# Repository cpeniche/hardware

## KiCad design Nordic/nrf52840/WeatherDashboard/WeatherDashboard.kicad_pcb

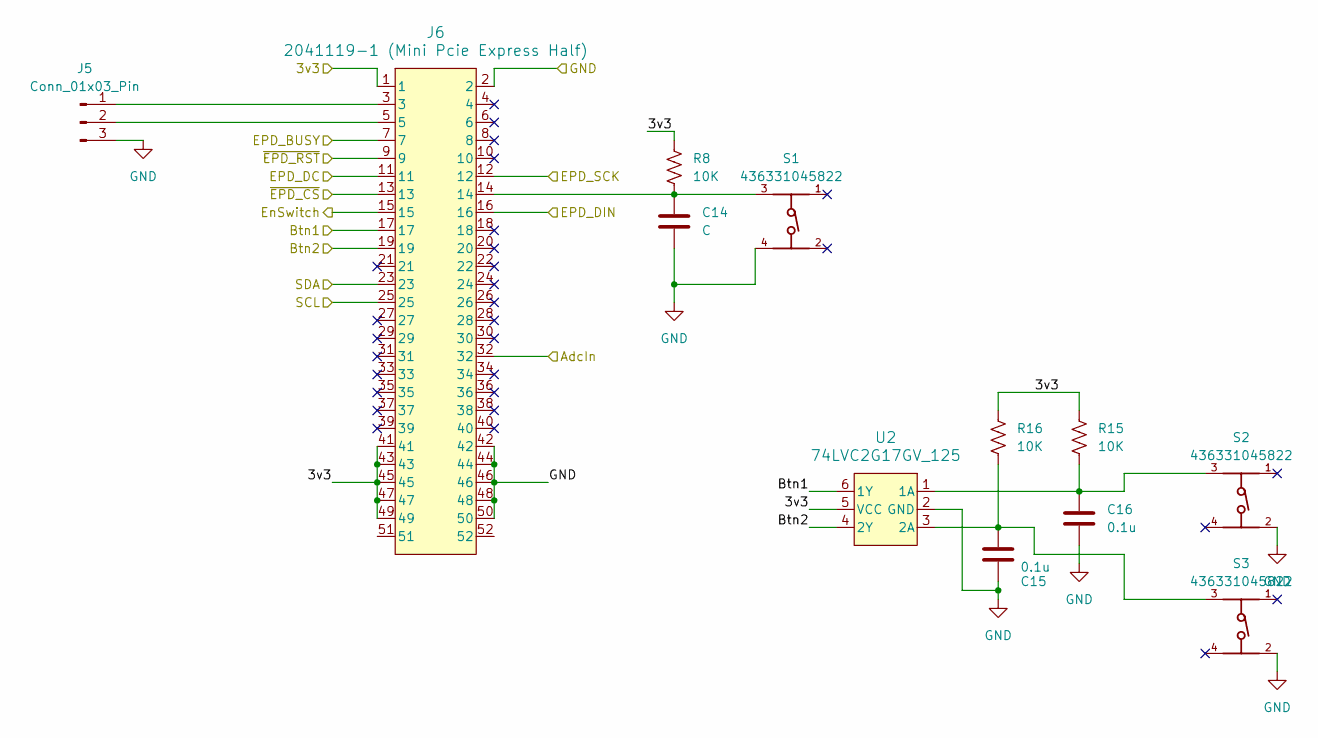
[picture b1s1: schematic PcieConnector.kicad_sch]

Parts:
C14: C; C_0805_2012Metric_Pad1.18x1.45mm_HandSolder
C15, C16: 0.1u; C_0402_1005Metric_Pad0.74x0.62mm_HandSolder
J5: Conn_01x03_Pin; PinSocket_1x03_P2.54mm_Vertical
J6: 2041119-1 (Mini Pcie Express Half); CONN_2041119-1_TEC
R8, R15, R16: 10K; R_0402_1005Metric_Pad0.72x0.64mm_HandSolder
S1, S2, S3: 436331045822; 4363X10458XX
U2: 74LVC2G17GV_125; SC-74_TSOP6_NEX

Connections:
/Display/3v3: J6.1, J6.41, J6.43, J6.45, J6.47, J6.49, R8.1, R15.1, R16.1, U2.5 (VCC); also elsewhere on the board
/Display/EPD_BUSY: J6.7; also elsewhere on the board
/Display/EPD_DC: J6.11; also elsewhere on the board
/Display/EPD_DIN: J6.16; also elsewhere on the board
/Display/EPD_SCK: J6.12; also elsewhere on the board
/Display/TSCL: J6.25; also elsewhere on the board
/Display/TSDA: J6.23; also elsewhere on the board
/Display/~EPD_CS: J6.13; also elsewhere on the board
/Display/~EPD_RST: J6.9; also elsewhere on the board
/Pcie Connector/AdcIn: J6.32; also elsewhere on the board
/Pcie Connector/Btn1: J6.17, U2.6 (1Y)
/Pcie Connector/Btn2: J6.19, U2.4 (2Y)
/Pcie Connector/EnSwitch: J6.15; also elsewhere on the board
GND: C14.2, C15.2, C16.2, J5.3, J6.2, J6.42, J6.44, J6.46, J6.48, J6.50, S1.4, S2.2, S3.2, U2.2 (GND); also elsewhere on the board
unnamed: C14.1, J6.14, R8.2, S1.3
unnamed: J5.1, J6.3
unnamed: J5.2, J6.5
unnamed: C16.1, R15.2, S2.3, U2.1 (1A)
unnamed: C15.1, R16.2, S3.3, U2.3 (2A)

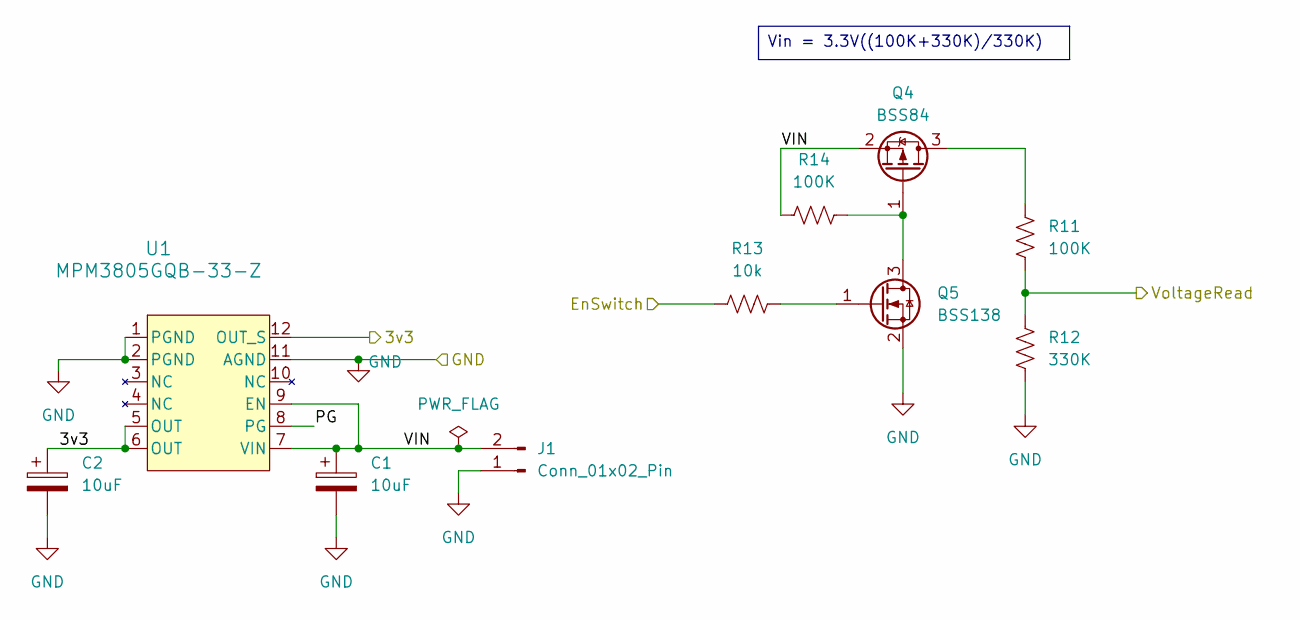
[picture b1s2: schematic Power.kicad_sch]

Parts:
C1, C2: 10uF; CP_EIA-3216-12_Kemet-S_HandSolder
J1: Conn_01x02_Pin; PinHeader_1x02_P2.54mm_Vertical
Q4: BSS84; SOT-23
Q5: BSS138; SOT-23
R11, R14: 100K; R_0402_1005Metric_Pad0.72x0.64mm_HandSolder
R12: 330K; R_0402_1005Metric_Pad0.72x0.64mm_HandSolder
R13: 10k; R_0402_1005Metric_Pad0.72x0.64mm_HandSolder
U1: MPM3805GQB-33-Z; QFN2p5x3p0x0p9_MNP

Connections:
/Display/3v3: C2.1, U1.5 (OUT), U1.6 (OUT), U1.12 (OUT_S); also elsewhere on the board
/Pcie Connector/AdcIn: R11.2, R12.1; also elsewhere on the board
/Pcie Connector/EnSwitch: R13.1; also elsewhere on the board
/Power/PG: U1.8 (PG)
/Power/VIN: C1.1, J1.2, Q4.2 (S), R14.1, U1.7 (VIN), U1.9 (EN)
GND: C1.2, C2.2, J1.1, Q5.2 (S), R12.2, U1.1 (PGND), U1.2 (PGND), U1.11 (AGND); also elsewhere on the board
unnamed: Q4.3 (D), R11.1
unnamed: Q4.1 (G), Q5.3 (D), R14.2
unnamed: Q5.1 (G), R13.2

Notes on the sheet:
Vin = 3.3V((100K+330K)/330K)

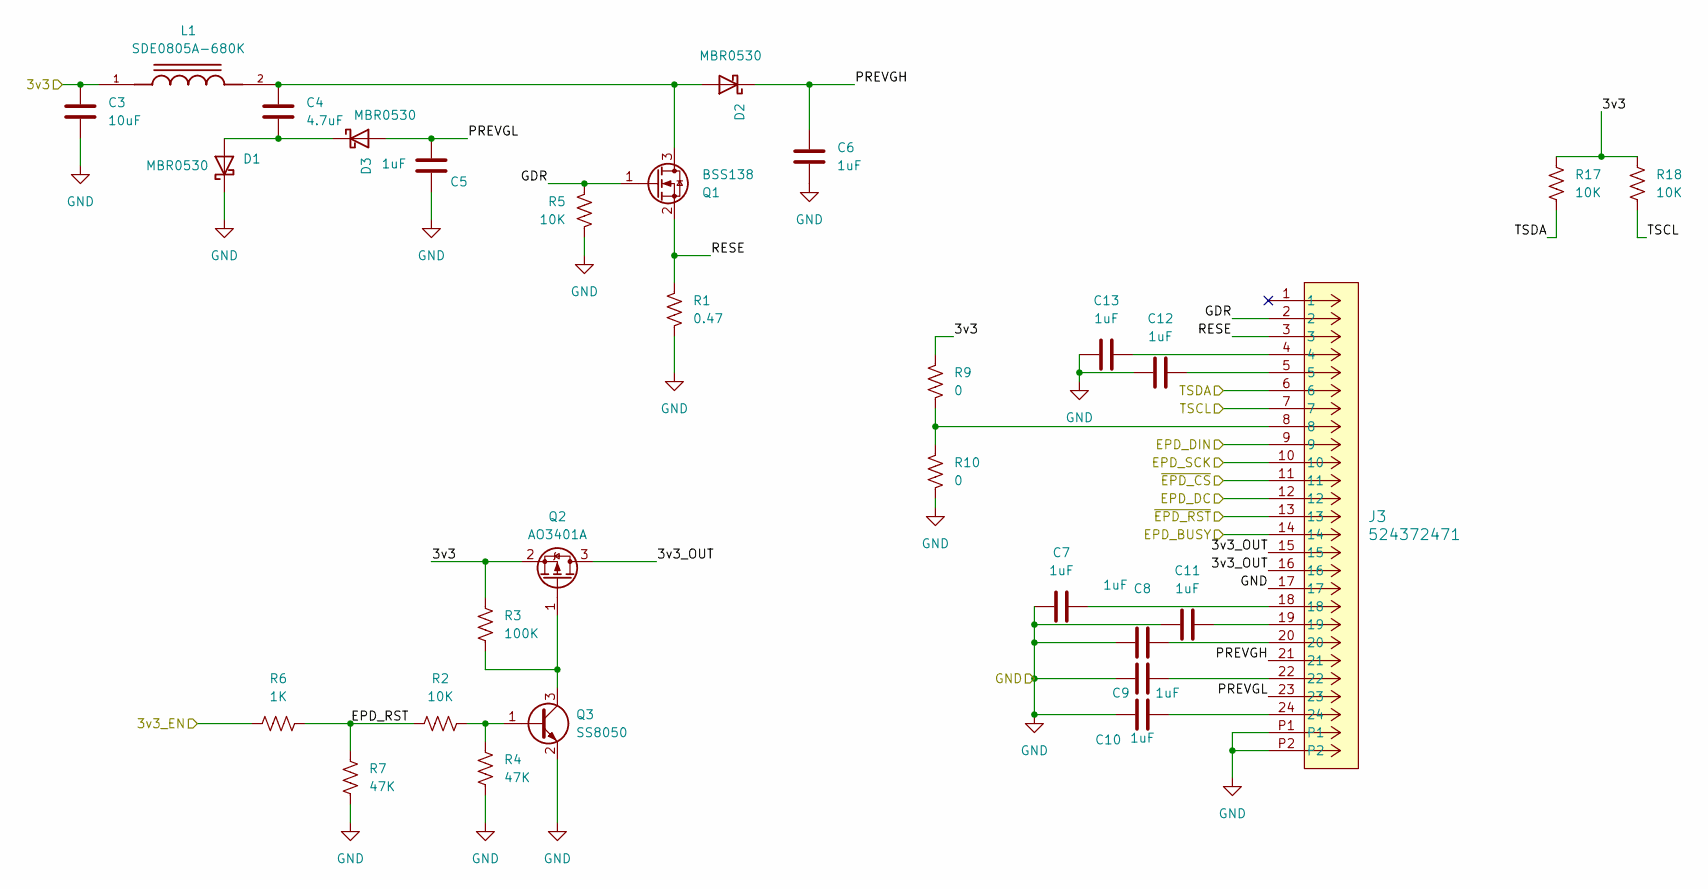
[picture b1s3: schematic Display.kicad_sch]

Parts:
C3: 10uF; C_0402_1005Metric_Pad0.74x0.62mm_HandSolder
C4: 4.7uF; C_0402_1005Metric_Pad0.74x0.62mm_HandSolder
C5, C6, C7, C8, C9, C10, C11, C12, C13: 1uF; C_0402_1005Metric_Pad0.74x0.62mm_HandSolder
D1, D2, D3: MBR0530; D_SOD-123
J3: 524372471; CON_524372471_MOL
L1: SDE0805A-680K; IND_SDE0805A-680K; PARTREV 11/19
Q1: BSS138; SOT-23_Handsoldering
Q2: AO3401A; SOT-23
Q3: SS8050; SOT-23_Handsoldering
R1: 0.47; R_0402_1005Metric_Pad0.72x0.64mm_HandSolder
R2, R5, R17, R18: 10K; R_0402_1005Metric_Pad0.72x0.64mm_HandSolder
R3: 100K; R_0402_1005Metric_Pad0.72x0.64mm_HandSolder
R4, R7: 47K; R_0402_1005Metric_Pad0.72x0.64mm_HandSolder
R6: 1K; R_0402_1005Metric_Pad0.72x0.64mm_HandSolder
R9, R10: 0; R_0402_1005Metric_Pad0.72x0.64mm_HandSolder

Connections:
/Display/3v3: C3.1, L1.1, Q2.2 (S), R3.1, R6.2, R9.1, R17.2, R18.2; also elsewhere on the board
/Display/3v3_OUT: J3.15, J3.16, Q2.3 (D)
/Display/EPD_BUSY: J3.14; also elsewhere on the board
/Display/EPD_DC: J3.12; also elsewhere on the board
/Display/EPD_DIN: J3.9; also elsewhere on the board
/Display/EPD_RST: R2.1, R6.1, R7.2
/Display/EPD_SCK: J3.10; also elsewhere on the board
/Display/GDR: J3.2, Q1.1 (G), R5.2
/Display/PREVGH: C6.1, D2.1 (K), J3.21
/Display/PREVGL: C5.1, D3.2 (A), J3.23
/Display/RESE: J3.3, Q1.2 (S), R1.1
/Display/TSCL: J3.7, R18.1; also elsewhere on the board
/Display/TSDA: J3.6, R17.1; also elsewhere on the board
/Display/~EPD_CS: J3.11; also elsewhere on the board
/Display/~EPD_RST: J3.13; also elsewhere on the board
GND: C3.2, C5.2, C6.2, C7.1, C8.1, C9.1, C10.1, C11.1, C12.1, C13.1, D1.1 (K), J3.17, J3.P1, J3.P2, Q3.2 (E), R1.2, R4.2, R5.1, R7.1, R10.2; also elsewhere on the board
unnamed: C7.2, J3.18
unnamed: C8.2, J3.20
unnamed: C9.2, J3.22
unnamed: C10.2, J3.24
unnamed: C11.2, J3.19
unnamed: C12.2, J3.5
unnamed: C13.2, J3.4
unnamed: C4.2, D1.2 (A), D3.1 (K)
unnamed: C4.1, D2.2 (A), L1.2, Q1.3 (D)
unnamed: J3.8, R9.2, R10.1
unnamed: Q2.1 (G), Q3.3 (C), R3.2
unnamed: Q3.1 (B), R2.2, R4.1

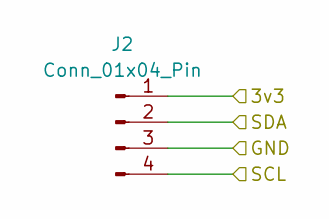
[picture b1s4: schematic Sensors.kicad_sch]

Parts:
J2: Conn_01x04_Pin; PinHeader_1x04_P2.54mm_Vertical

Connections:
/Display/3v3: J2.1; also elsewhere on the board
/Display/TSCL: J2.4; also elsewhere on the board
/Display/TSDA: J2.2; also elsewhere on the board
GND: J2.3; also elsewhere on the board

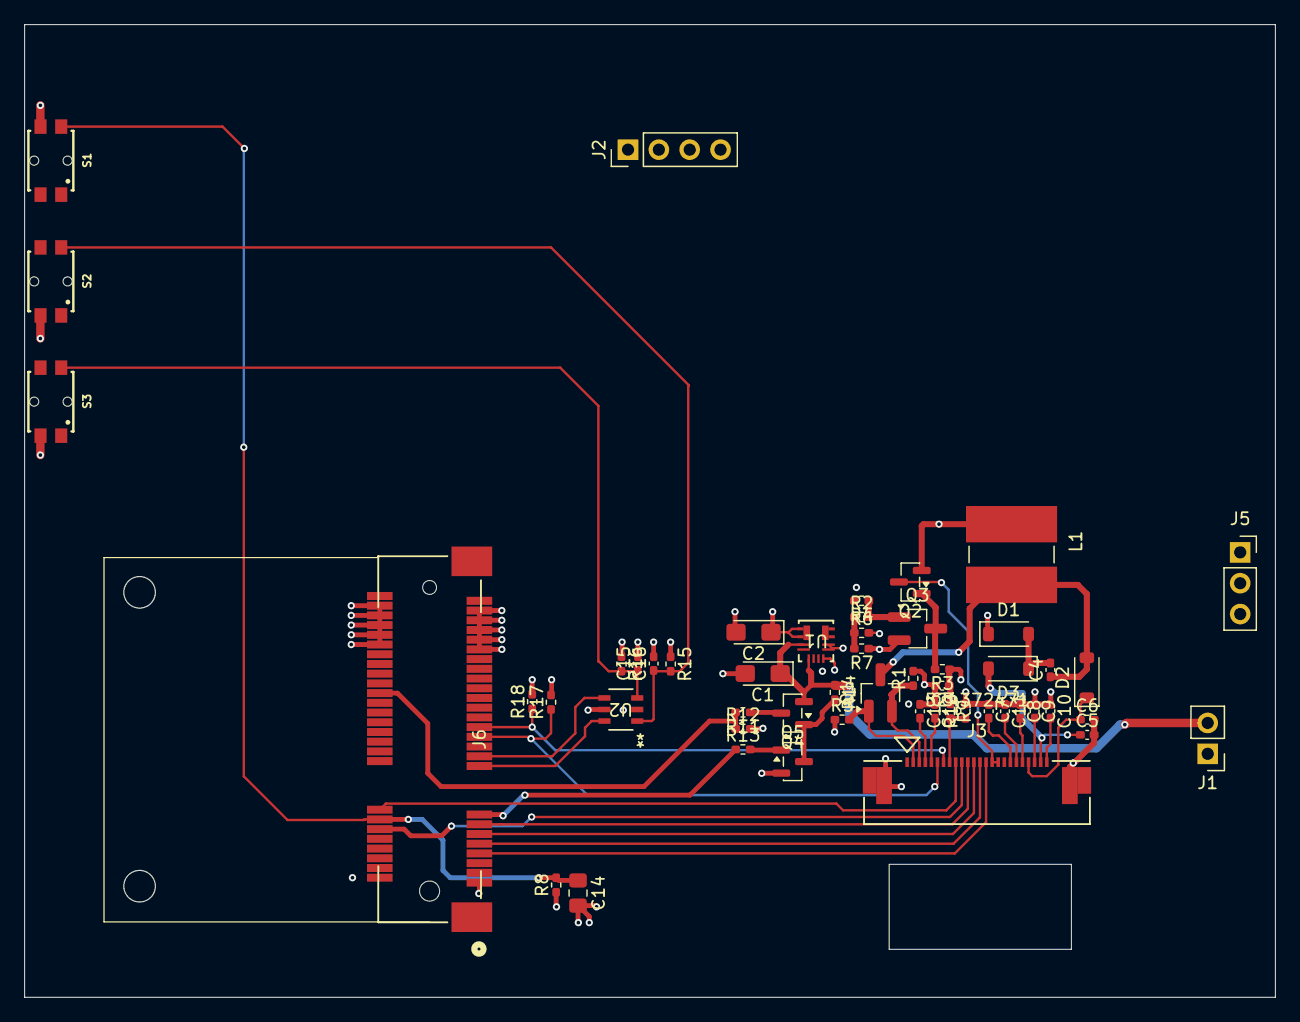
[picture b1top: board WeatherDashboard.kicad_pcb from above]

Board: 4 copper layers, 102.9 x 80.0 mm, 53 parts (0 on the bottom side), 41 nets.

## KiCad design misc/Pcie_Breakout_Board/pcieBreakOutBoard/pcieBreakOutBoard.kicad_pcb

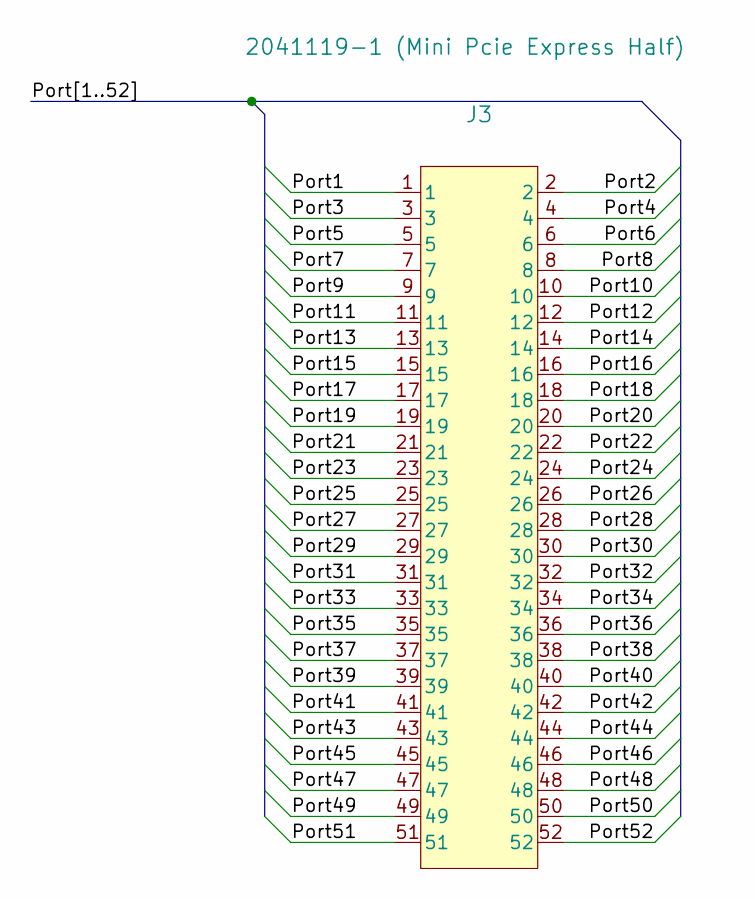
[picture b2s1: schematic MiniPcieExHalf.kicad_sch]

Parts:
J3: 2041119-1 (Mini Pcie Express Half); BUS_PCI_Express_Mini_Half

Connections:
/MiniPcieExHalf/Port1: J3.1
/MiniPcieExHalf/Port2: J3.2
/MiniPcieExHalf/Port3: J3.3
/MiniPcieExHalf/Port4: J3.4
/MiniPcieExHalf/Port5: J3.5
/MiniPcieExHalf/Port6: J3.6
/MiniPcieExHalf/Port7: J3.7
/MiniPcieExHalf/Port8: J3.8
/MiniPcieExHalf/Port9: J3.9
/MiniPcieExHalf/Port10: J3.10
/MiniPcieExHalf/Port11: J3.11
/MiniPcieExHalf/Port12: J3.12
/MiniPcieExHalf/Port13: J3.13
/MiniPcieExHalf/Port14: J3.14
/MiniPcieExHalf/Port15: J3.15
/MiniPcieExHalf/Port16: J3.16
/MiniPcieExHalf/Port17: J3.17
/MiniPcieExHalf/Port18: J3.18
/MiniPcieExHalf/Port19: J3.19
/MiniPcieExHalf/Port20: J3.20
/MiniPcieExHalf/Port21: J3.21
/MiniPcieExHalf/Port22: J3.22
/MiniPcieExHalf/Port23: J3.23
/MiniPcieExHalf/Port24: J3.24
/MiniPcieExHalf/Port25: J3.25
/MiniPcieExHalf/Port26: J3.26
/MiniPcieExHalf/Port27: J3.27
/MiniPcieExHalf/Port28: J3.28
/MiniPcieExHalf/Port29: J3.29
/MiniPcieExHalf/Port30: J3.30
/MiniPcieExHalf/Port31: J3.31
/MiniPcieExHalf/Port32: J3.32
/MiniPcieExHalf/Port33: J3.33
/MiniPcieExHalf/Port34: J3.34
/MiniPcieExHalf/Port35: J3.35
/MiniPcieExHalf/Port36: J3.36
/MiniPcieExHalf/Port37: J3.37
/MiniPcieExHalf/Port38: J3.38
/MiniPcieExHalf/Port39: J3.39
/MiniPcieExHalf/Port40: J3.40
/MiniPcieExHalf/Port41: J3.41
/MiniPcieExHalf/Port42: J3.42
/MiniPcieExHalf/Port43: J3.43
/MiniPcieExHalf/Port44: J3.44
/MiniPcieExHalf/Port45: J3.45
/MiniPcieExHalf/Port46: J3.46
/MiniPcieExHalf/Port47: J3.47
/MiniPcieExHalf/Port48: J3.48
/MiniPcieExHalf/Port49: J3.49
/MiniPcieExHalf/Port50: J3.50
/MiniPcieExHalf/Port51: J3.51
/MiniPcieExHalf/Port52: J3.52

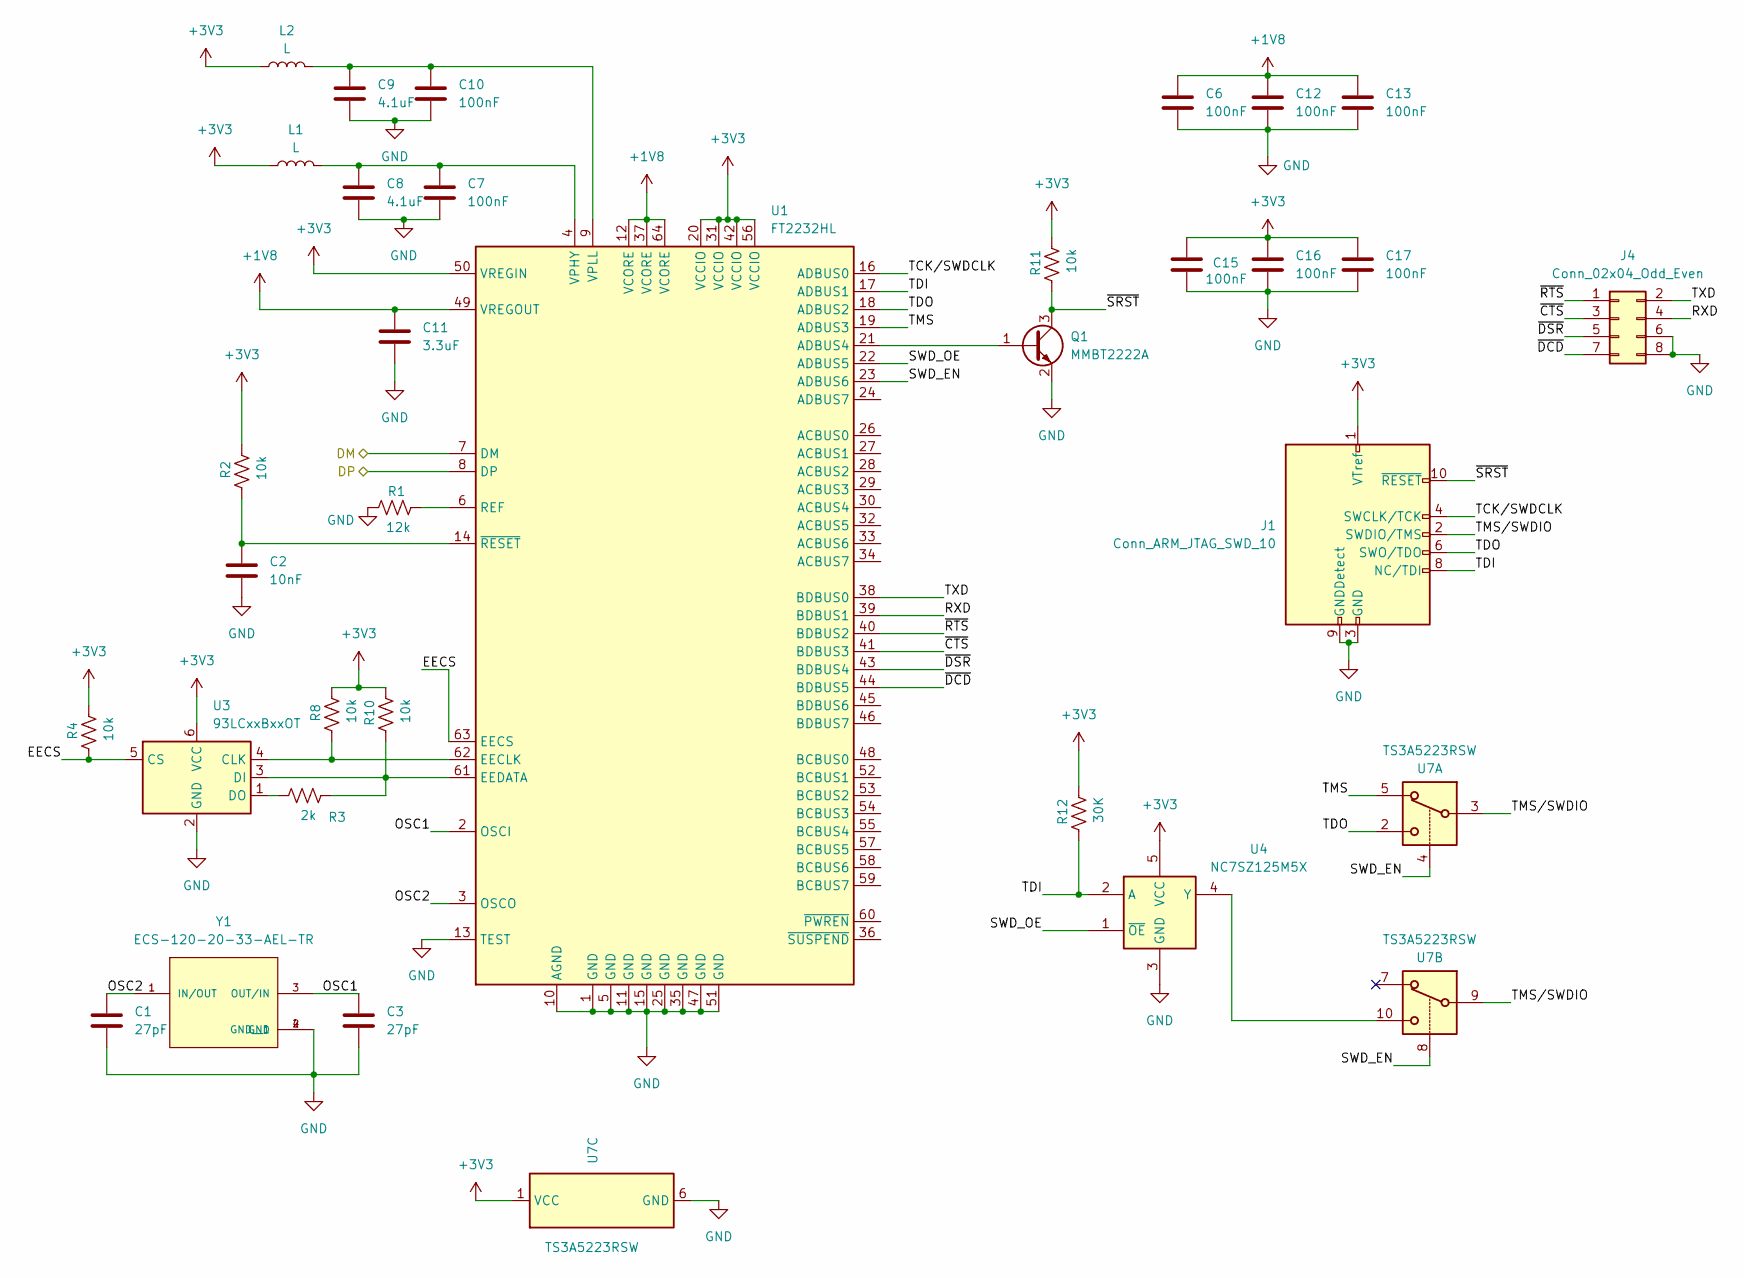
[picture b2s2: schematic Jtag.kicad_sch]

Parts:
C1, C3: 27pF; C_0402_1005Metric_Pad0.74x0.62mm_HandSolder
C2: 10nF; C_0402_1005Metric_Pad0.74x0.62mm_HandSolder
C6, C7, C10, C12, C13, C15, C16, C17: 100nF; C_0402_1005Metric_Pad0.74x0.62mm_HandSolder
C8, C9: 4.1uF; C_0402_1005Metric_Pad0.74x0.62mm_HandSolder
C11: 3.3uF; C_0402_1005Metric_Pad0.74x0.62mm_HandSolder
J1: Conn_ARM_JTAG_SWD_10; PinHeader_2x05_P1.27mm_Vertical
J4: Conn_02x04_Odd_Even; PinHeader_2x04_P2.54mm_Vertical
L1, L2: L; L_0402_1005Metric_Pad0.77x0.64mm_HandSolder
Q1: MMBT2222A; SOT-23_Handsoldering
R1: 12k; R_0402_1005Metric_Pad0.72x0.64mm_HandSolder
R2, R4, R8, R10, R11: 10k; R_0402_1005Metric_Pad0.72x0.64mm_HandSolder
R3: 2k; R_0402_1005Metric_Pad0.72x0.64mm_HandSolder
R12: 30K; R_0402_1005Metric_Pad0.72x0.64mm_HandSolder
U1: FT2232HL; LQFP-64_10x10mm_P0.5mm
U3: 93LCxxBxxOT; SOT-23-6
U4: NC7SZ125M5X; SOT-23-5
U7: TS3A5223RSW; Texas_RSW0010A_UQFN-10_1.4x1.8mm_P0.4mm
Y1: ECS-120-20-33-AEL-TR; XTAL_ECS-120-20-33-AEL-TR

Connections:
+1V8: C6.1, C11.1, C12.1, C13.1, U1.12 (VCORE), U1.37 (VCORE), U1.49 (VREGOUT), U1.64 (VCORE)
+3V3: C15.1, C16.1, C17.1, J1.1 (VTref), L1.1, L2.1, R2.2, R4.2, R8.2, R10.2, R11.2, R12.2, U1.20 (VCCIO), U1.31 (VCCIO), U1.42 (VCCIO), U1.50 (VREGIN), U1.56 (VCCIO), U3.6 (VCC), U4.5 (VCC), U7.1 (VCC); also elsewhere on the board
/Jtag/DM: U1.7 (DM)
/Jtag/DP: U1.8 (DP)
/Jtag/EECS: R4.1, U1.63 (EECS), U3.5 (CS)
/Jtag/OSC1: C3.1, U1.2 (OSCI), Y1.3 (OUT/IN)
/Jtag/OSC2: C1.1, U1.3 (OSCO), Y1.1 (IN/OUT)
/Jtag/RXD: J4.4, U1.39 (BDBUS1)
/Jtag/SWD_EN: U1.23 (ADBUS6), U7.4, U7.8
/Jtag/SWD_OE: U1.22 (ADBUS5), U4.1 (~OE)
/Jtag/TCK/SWDCLK: J1.4 (SWCLK/TCK), U1.16 (ADBUS0)
/Jtag/TDI: J1.8 (NC/TDI), R12.1, U1.17 (ADBUS1), U4.2 (A)
/Jtag/TDO: J1.6 (SWO/TDO), U1.18 (ADBUS2), U7.2
/Jtag/TMS: U1.19 (ADBUS3), U7.5
/Jtag/TMS/SWDIO: J1.2 (SWDIO/TMS), U7.3, U7.9
/Jtag/TXD: J4.2, U1.38 (BDBUS0)
/Jtag/~CTS: J4.3, U1.41 (BDBUS3)
/Jtag/~DCD: J4.7, U1.44 (BDBUS5)
/Jtag/~DSR: J4.5, U1.43 (BDBUS4)
/Jtag/~RTS: J4.1, U1.40 (BDBUS2)
/Jtag/~SRST: J1.10 (~RESET), Q1.3 (C), R11.1
GND: C1.2, C2.2, C3.2, C6.2, C7.2, C8.2, C9.2, C10.2, C11.2, C12.2, C13.2, C15.2, C16.2, C17.2, J1.3 (GND), J1.5 (GND), J1.9 (GNDDetect), J4.6, J4.8, Q1.2 (E), R1.1, U1.1 (GND), U1.5 (GND), U1.10 (AGND), U1.11 (GND), U1.13 (TEST), U1.15 (GND), U1.25 (GND), U1.35 (GND), U1.47 (GND), U1.51 (GND), U3.2 (GND), U4.3 (GND), U7.6 (GND), Y1.2 (GND), Y1.4 (GND__1); also elsewhere on the board
unnamed: Q1.1 (B), U1.21 (ADBUS4)
unnamed: R8.1, U1.62 (EECLK), U3.4 (CLK)
unnamed: R3.2, R10.1, U1.61 (EEDATA), U3.3 (DI)
unnamed: R1.2, U1.6 (REF)
unnamed: C7.1, C8.1, L1.2, U1.4 (VPHY)
unnamed: C9.1, C10.1, L2.2, U1.9 (VPLL)
unnamed: C2.1, R2.1, U1.14 (~RESET)
unnamed: R3.1, U3.1 (DO)
unnamed: U4.4 (Y), U7.10

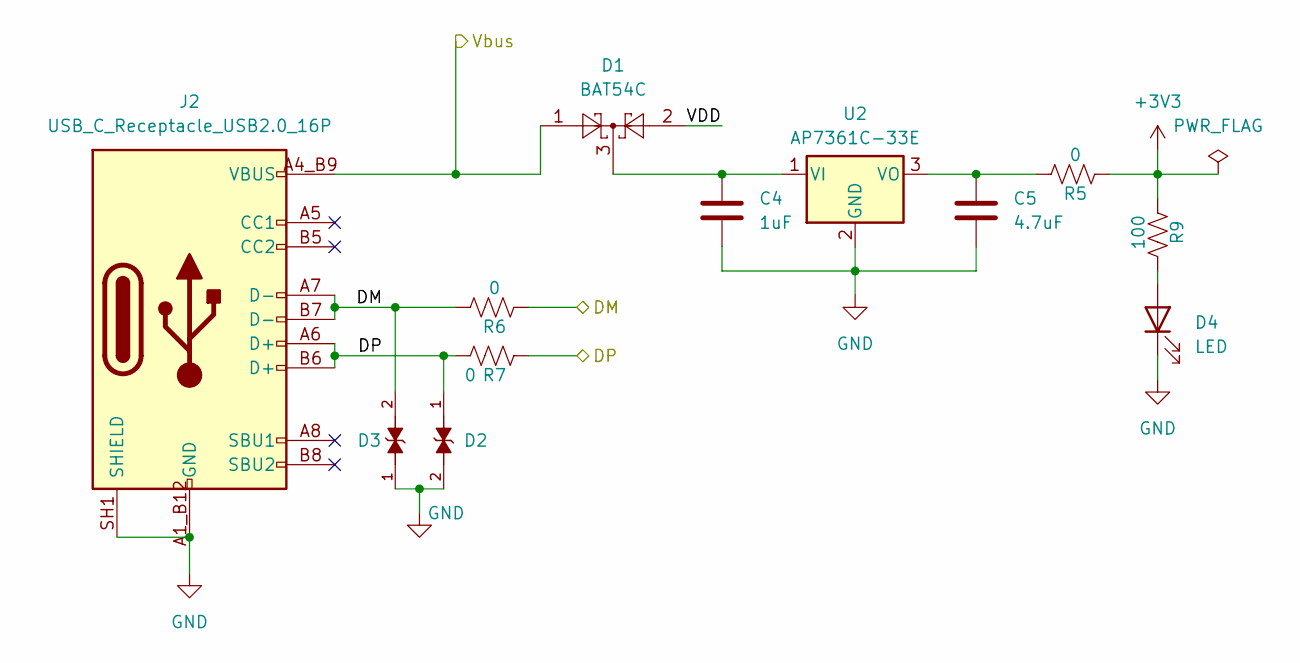
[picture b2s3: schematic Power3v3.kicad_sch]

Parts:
C4: 1uF; C_0402_1005Metric_Pad0.74x0.62mm_HandSolder
C5: 4.7uF; C_0402_1005Metric_Pad0.74x0.62mm_HandSolder
D1: BAT54C; SOT-23
D2, D3: PGB1010603NR; DIOC1608X36N
D4: LED; LED_0402_1005Metric
J2: USB_C_Receptacle_USB2.0_16P; AMPHENOL_GSB1C41110SSHR; PARTREV AX1
R5, R6, R7: 0; R_0402_1005Metric_Pad0.72x0.64mm_HandSolder
R9: 100; R_0402_1005Metric_Pad0.72x0.64mm_HandSolder
U2: AP7361C-33E; SOT-223-3_TabPin2

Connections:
+3V3: R5.2, R9.2; also elsewhere on the board
/Power/DM: D3.2, J2.A7 (D-), J2.B7 (D-), R6.1, R6.2
/Power/DP: D2.1, J2.A6 (D+), J2.B6 (D+), R7.1, R7.2
/Power/VDD: D1.2
/Power/Vbus: D1.1, J2.A4_B9 (VBUS), J2.B4_A9 (VBUS)
GND: C4.2, C5.2, D2.2, D3.1, D4.1 (K), J2.A1_B12 (GND), J2.B1_A12 (GND), J2.SH1 (SHIELD), U2.2 (GND); also elsewhere on the board
unnamed: D4.2 (A), R9.1
unnamed: C4.1, D1.3, U2.1 (VI)
unnamed: C5.1, R5.1, U2.3 (VO)

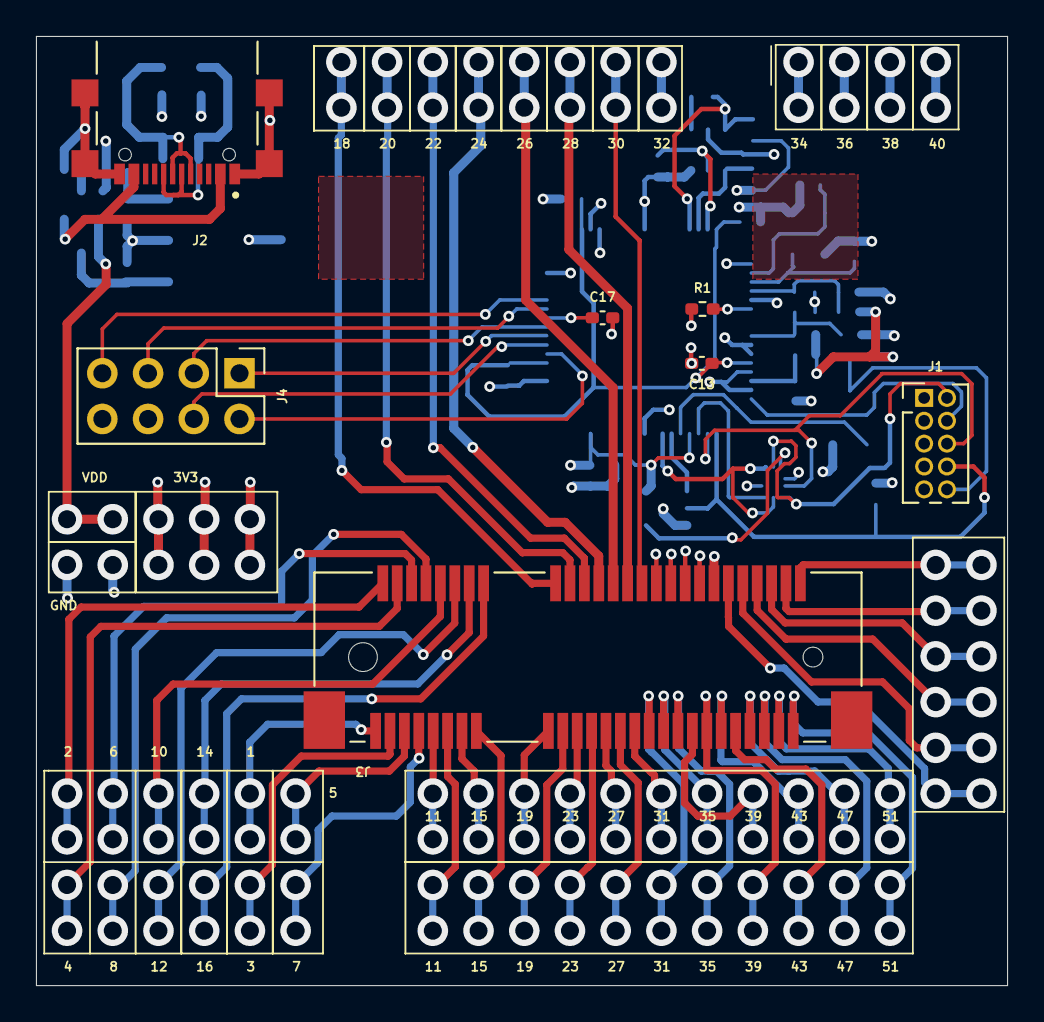
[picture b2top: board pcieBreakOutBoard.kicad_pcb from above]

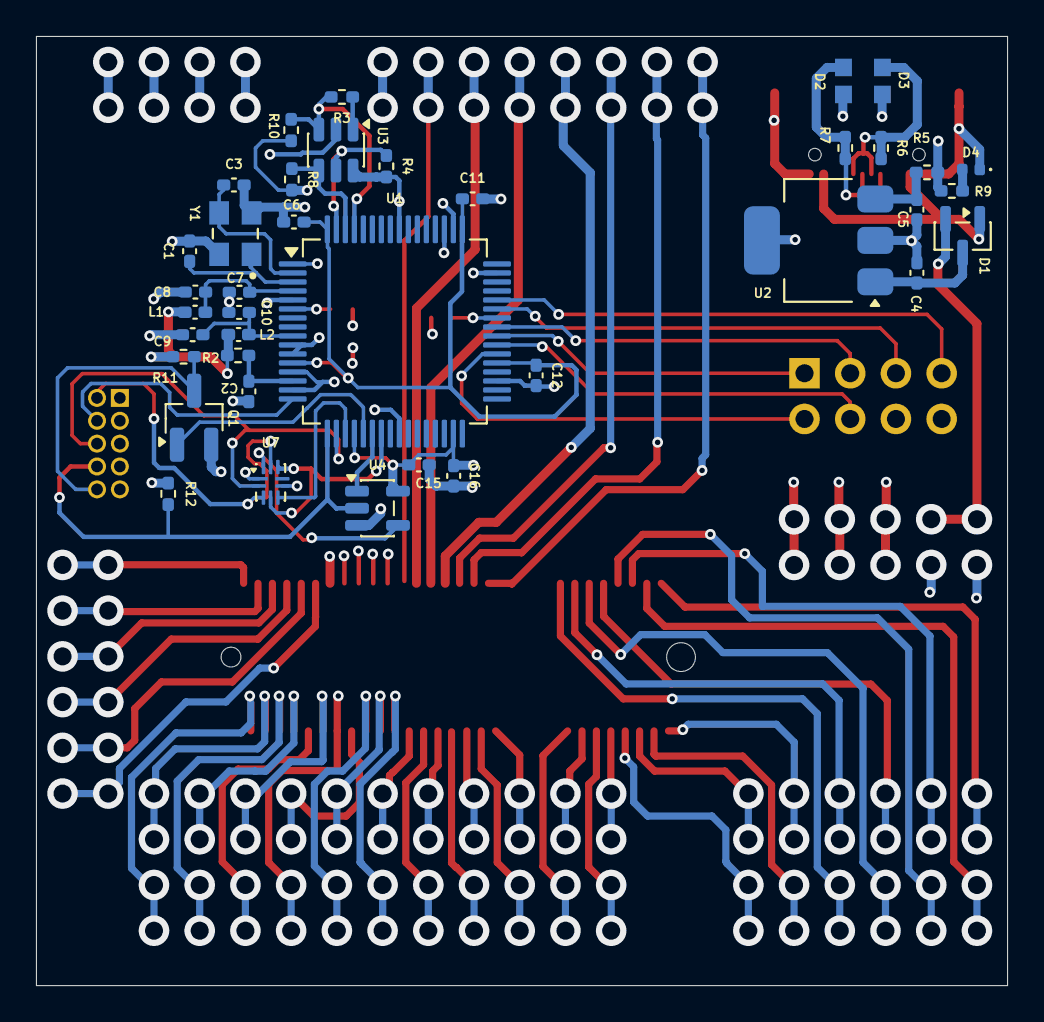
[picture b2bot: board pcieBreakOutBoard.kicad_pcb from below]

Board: 4 copper layers, 54.0 x 52.7 mm, 45 parts (38 on the bottom side), 35 nets.

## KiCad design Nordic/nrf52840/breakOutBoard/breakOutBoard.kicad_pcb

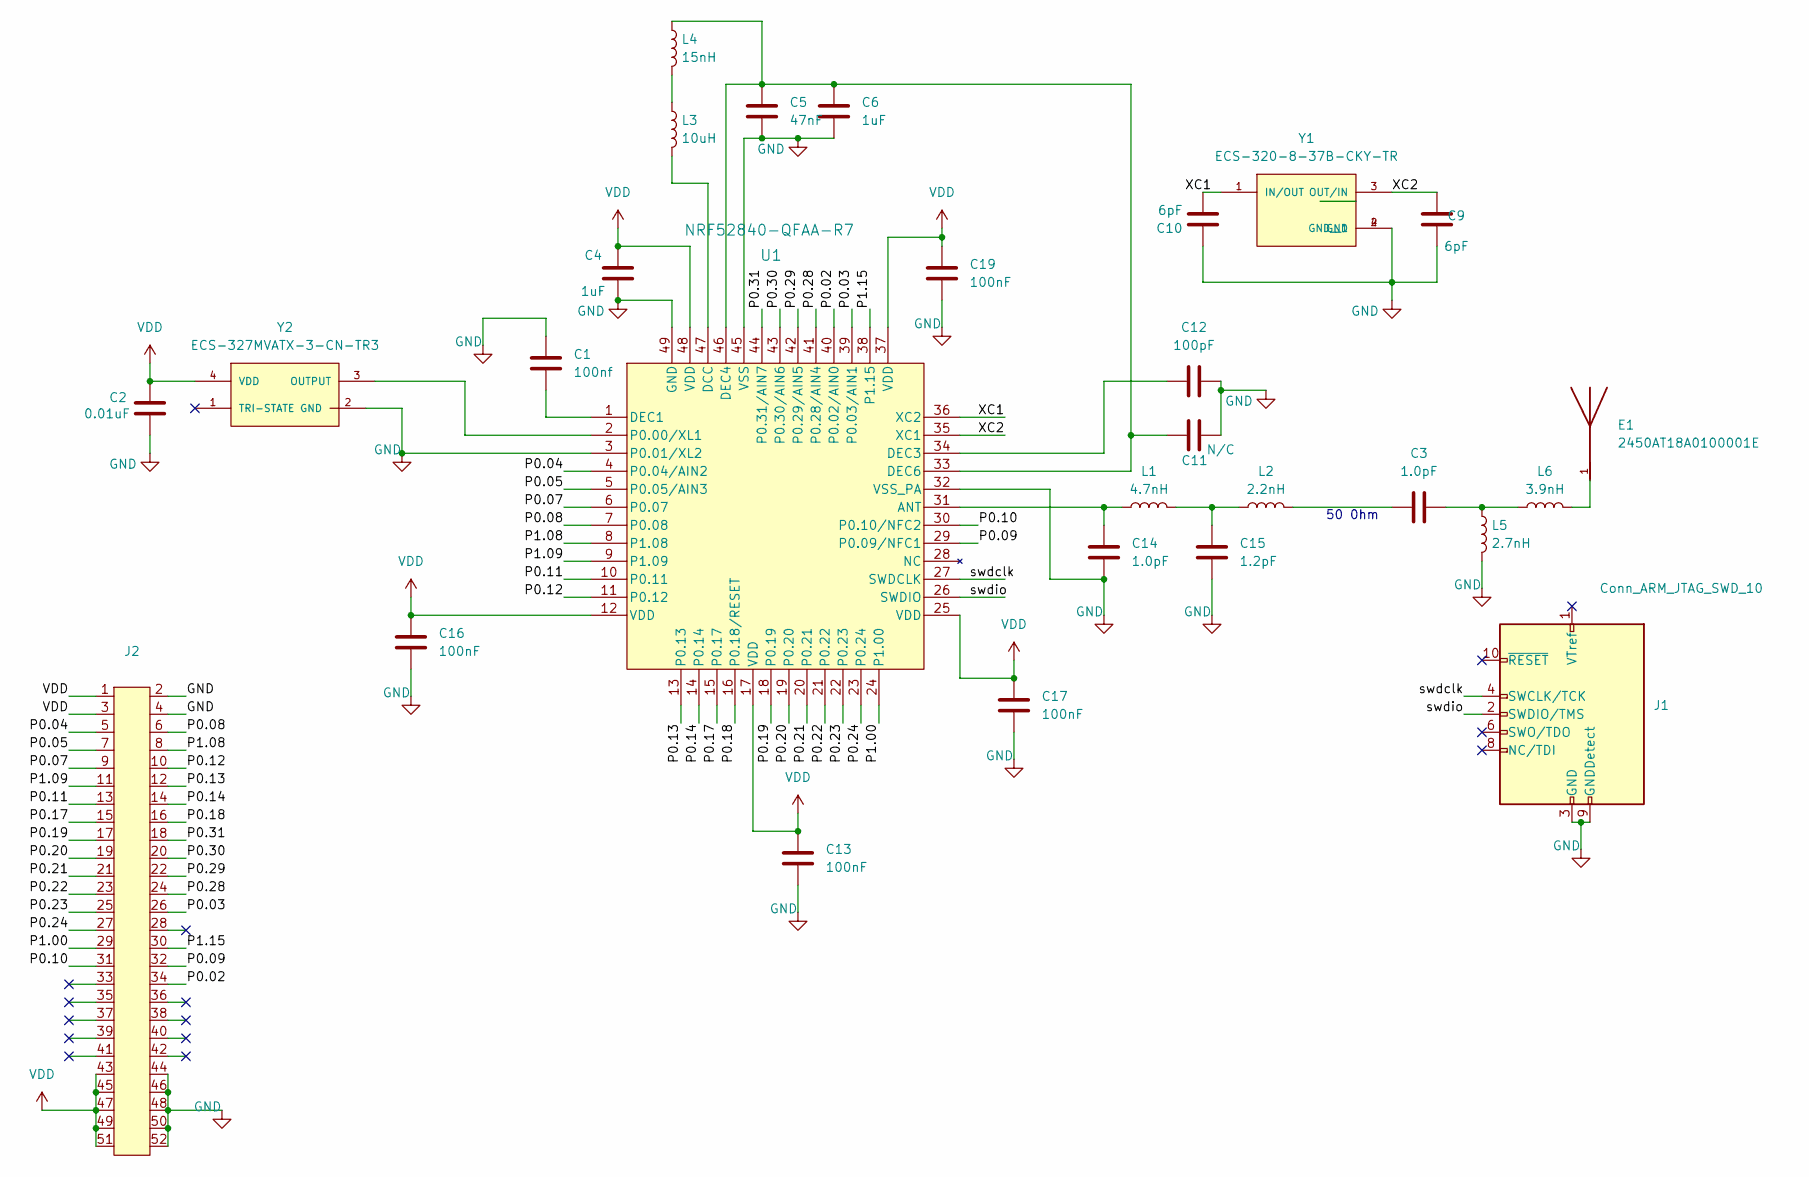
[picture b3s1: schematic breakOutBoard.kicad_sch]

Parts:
C1: 100nf; C_0201_0603Metric
C2: 0.01uF; C_0201_0603Metric
C3, C14: 1.0pF; C_0201_0603Metric
C4, C6: 1uF; C_0201_0603Metric
C5: 47nF; C_0201_0603Metric
C9, C10: 6pF; C_0201_0603Metric
C11: N/C; C_0201_0603Metric
C12: 100pF; C_0201_0603Metric
C13, C16, C17, C19: 100nF; C_0201_0603Metric
C15: 1.2pF; C_0201_0603Metric
E1: 2450AT18A0100001E; XCVR_2450AT18A0100001E; PARTREV 4.0
J1: Conn_ARM_JTAG_SWD_10; PinHeader_2x05_P1.27mm_Vertical
J2: Mini PCI express Half
L1: 4.7nH; L_0201_0603Metric
L2: 2.2nH; L_0201_0603Metric
L3: 10uH; L_0603_1608Metric
L4: 15nH; L_0201_0603Metric
L5: 2.7nH; L_0201_0603Metric
L6: 3.9nH; L_0201_0603Metric
U1: NRF52840-QFAA-R7; QFN-48-1EP_6x6mm_P0.4mm_EP4.6x4.6mm
Y1: ECS-320-8-37B-CKY-TR; XTAL_ECS-160-9-37-CKM-TR; PARTREV 2017
Y2: ECS-327MVATX-3-CN-TR3; OSC_ECS-2333-160-BN-TR; PARTREV N/A

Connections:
/P0.02: J2.34, U1.40 (P0.02/AIN0)
/P0.03: J2.26, U1.39 (P0.03/AIN1)
/P0.04: J2.5, U1.4 (P0.04/AIN2)
/P0.05: J2.7, U1.5 (P0.05/AIN3)
/P0.07: J2.9, U1.6 (P0.07)
/P0.08: J2.6, U1.7 (P0.08)
/P0.09: J2.32, U1.29 (P0.09/NFC1)
/P0.10: J2.31, U1.30 (P0.10/NFC2)
/P0.11: J2.13, U1.10 (P0.11)
/P0.12: J2.10, U1.11 (P0.12)
/P0.13: J2.12, U1.13 (P0.13)
/P0.14: J2.14, U1.14 (P0.14)
/P0.17: J2.15, U1.15 (P0.17)
/P0.18: J2.16, U1.16 (P0.18/RESET)
/P0.19: J2.17, U1.18 (P0.19)
/P0.20: J2.19, U1.19 (P0.20)
/P0.21: J2.21, U1.20 (P0.21)
/P0.22: J2.23, U1.21 (P0.22)
/P0.23: J2.25, U1.22 (P0.23)
/P0.24: J2.27, U1.23 (P0.24)
/P0.28: J2.24, U1.41 (P0.28/AIN4)
/P0.29: J2.22, U1.42 (P0.29/AIN5)
/P0.30: J2.20, U1.43 (P0.30/AIN6)
/P0.31: J2.18, U1.44 (P0.31/AIN7)
/P1.00: J2.29, U1.24 (P1.00)
/P1.08: J2.8, U1.8 (P1.08)
/P1.09: J2.11, U1.9 (P1.09)
/P1.15: J2.30, U1.38 (P1.15)
/XC1: C10.2, U1.36 (XC2), Y1.1 (IN/OUT)
/XC2: C9.2, U1.35 (XC1), Y1.3 (OUT/IN)
/swdclk: J1.4 (SWCLK/TCK), U1.27 (SWDCLK)
/swdio: J1.2 (SWDIO/TMS), U1.26 (SWDIO)
GND: C1.1, C2.2, C4.2, C5.2, C6.2, C9.1, C10.1, C11.2, C12.2, C13.2, C14.2, C15.2, C16.2, C17.2, C19.2, J1.3 (GND), J1.5 (GND), J1.9 (GNDDetect), J2.2, J2.4, J2.44, J2.46, J2.48, J2.50, J2.52, L5.2, U1.3 (P0.01/XL2), U1.32 (VSS_PA), U1.45 (VSS), U1.49 (GND), Y1.2 (GND), Y1.4 (GND__1), Y2.2 (GND)
unnamed: C3.1, L2.2
unnamed: C3.2, L5.1, L6.1
unnamed: C15.1, L1.2, L2.1
unnamed: E1.1, L6.2
unnamed: L3.1, L4.2
unnamed: C14.1, L1.1, U1.31 (ANT)
unnamed: L3.2, U1.47 (DCC)
unnamed: C1.2, U1.1 (DEC1)
unnamed: C12.1, U1.34 (DEC3)
unnamed: C5.1, C6.1, C11.1, L4.1, U1.33 (DEC6), U1.46 (DEC4)
unnamed: U1.2 (P0.00/XL1), Y2.3 (OUTPUT)
VDD: C2.1, C4.1, C13.1, C16.1, C17.1, C19.1, J2.1, J2.3, J2.43, J2.45, J2.47, J2.49, J2.51, U1.12 (VDD), U1.17 (VDD), U1.25 (VDD), U1.37 (VDD), U1.48 (VDD), Y2.4 (VDD)

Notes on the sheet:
50 0hm

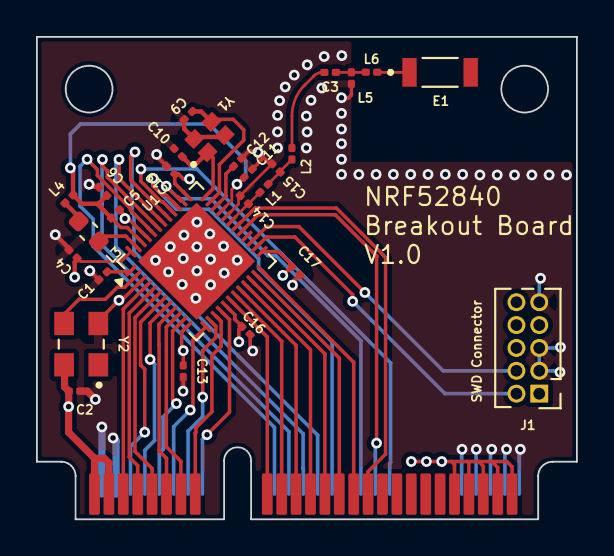
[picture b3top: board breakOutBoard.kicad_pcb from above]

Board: 4 copper layers, 30.0 x 26.8 mm, 28 parts (0 on the bottom side), 45 nets.

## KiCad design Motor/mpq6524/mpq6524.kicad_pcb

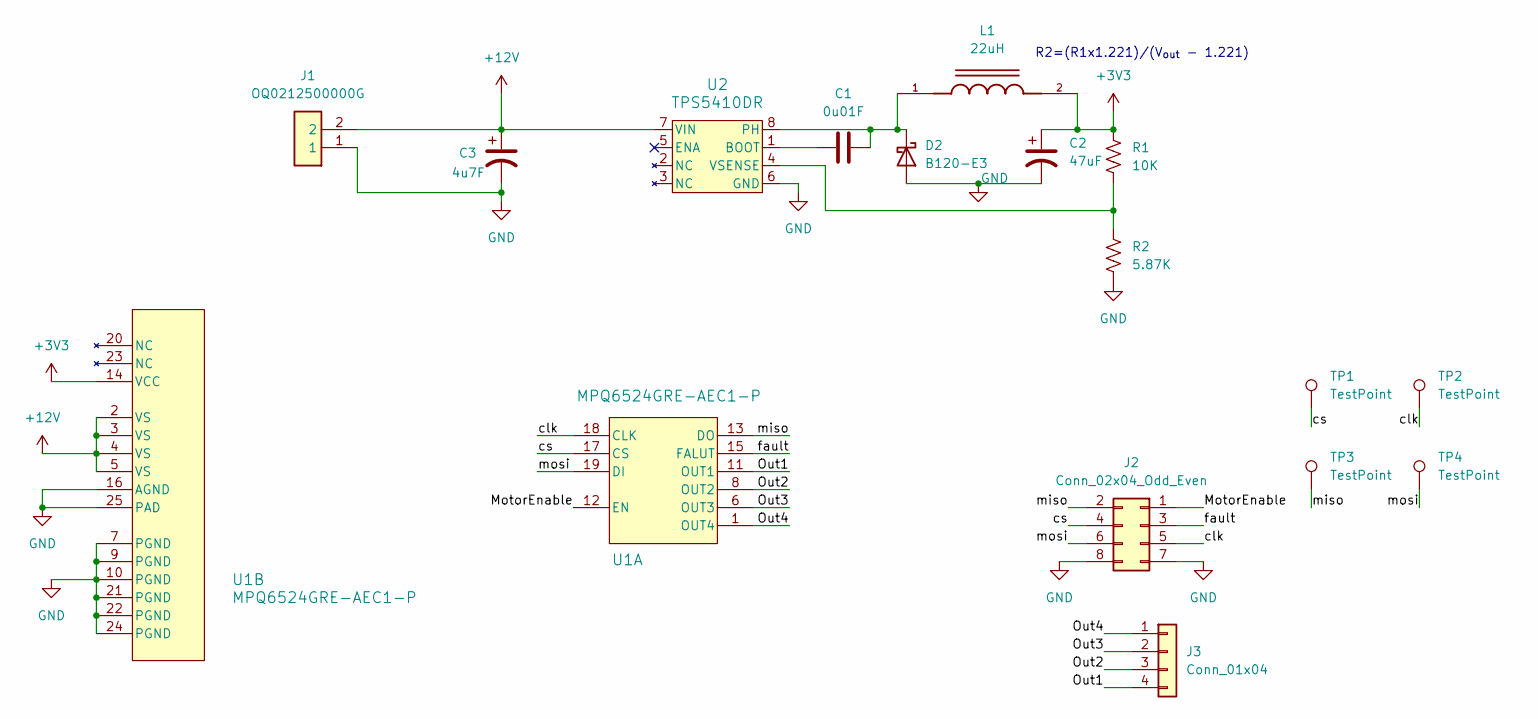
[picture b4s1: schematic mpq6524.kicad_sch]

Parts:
C1: 0u01F; C_0805_2012Metric_Pad1.18x1.45mm_HandSolder
C2: 47uF; CP_EIA-3216-10_Kemet-I_HandSolder
C3: 4u7F; CP_EIA-3528-21_Kemet-B_HandSolder
D2: B120-E3; D_SMA
J1: OQ0212500000G; Mouser Part Number 649-220107-C021A01LF
J2: Conn_02x04_Odd_Even; PinHeader_2x04_P2.54mm_Vertical
J3: Conn_01x04; PinHeader_1x04_P2.54mm_Vertical
L1: 22uH; IND_ASPI-0315FS-220M-T2; PARTREV 11/19/2021
R1: 10K; R_0805_2012Metric_Pad1.20x1.40mm_HandSolder
R2: 5.87K; R_0805_2012Metric_Pad1.20x1.40mm_HandSolder
TP1, TP2, TP3, TP4: TestPoint; TestPoint_Loop_D1.80mm_Drill1.0mm_Beaded
U1: MPQ6524GRE-AEC1-P; QFN-24-1EP_4x4mm_P0.5mm_EP2.5x2.5mm
U2: TPS5410DR; SOIC-8-1EP_3.9x4.9mm_P1.27mm

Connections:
+3V3: C2.1, L1.2, R1.1, U1.14 (VCC)
+12V: C3.1, J1.2, U1.2 (VS), U1.3 (VS), U1.4 (VS), U1.5 (VS), U2.7 (VIN)
/MotorEnable: J2.1, U1.12 (EN)
/Out1: J3.4, U1.11 (OUT1)
/Out2: J3.3, U1.8 (OUT2)
/Out3: J3.2, U1.6 (OUT3)
/Out4: J3.1, U1.1 (OUT4)
/clk: J2.5, TP2.1, U1.18 (CLK)
/cs: J2.4, TP1.1, U1.17 (CS)
/fault: J2.3, U1.15 (FALUT)
/miso: J2.2, TP3.1, U1.13 (DO)
/mosi: J2.6, TP4.1, U1.19 (DI)
GND: C2.2, C3.2, D2.2 (A), J1.1, J2.7, J2.8, R2.2, U1.7 (PGND), U1.9 (PGND), U1.10 (PGND), U1.16 (AGND), U1.21 (PGND), U1.22 (PGND), U1.24 (PGND), U1.25 (PAD), U2.6 (GND)
unnamed: C1.2, D2.1 (K), L1.1, U2.8 (PH)
unnamed: C1.1, U2.1 (BOOT)
unnamed: R1.2, R2.1, U2.4 (VSENSE)

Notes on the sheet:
R2=(R1x1.221)/(V_{out} - 1.221)
